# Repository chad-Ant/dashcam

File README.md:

# dashcam
Dashcam software for my own car. Hardware includes:
 - 1 IMX296 color camera facing front for recording and inference work, set at 1080p@60fps
 - 2 USB cameras for range finding, 360p@10fps
 - 1 USB camera for driver behavior, 360p@10fps

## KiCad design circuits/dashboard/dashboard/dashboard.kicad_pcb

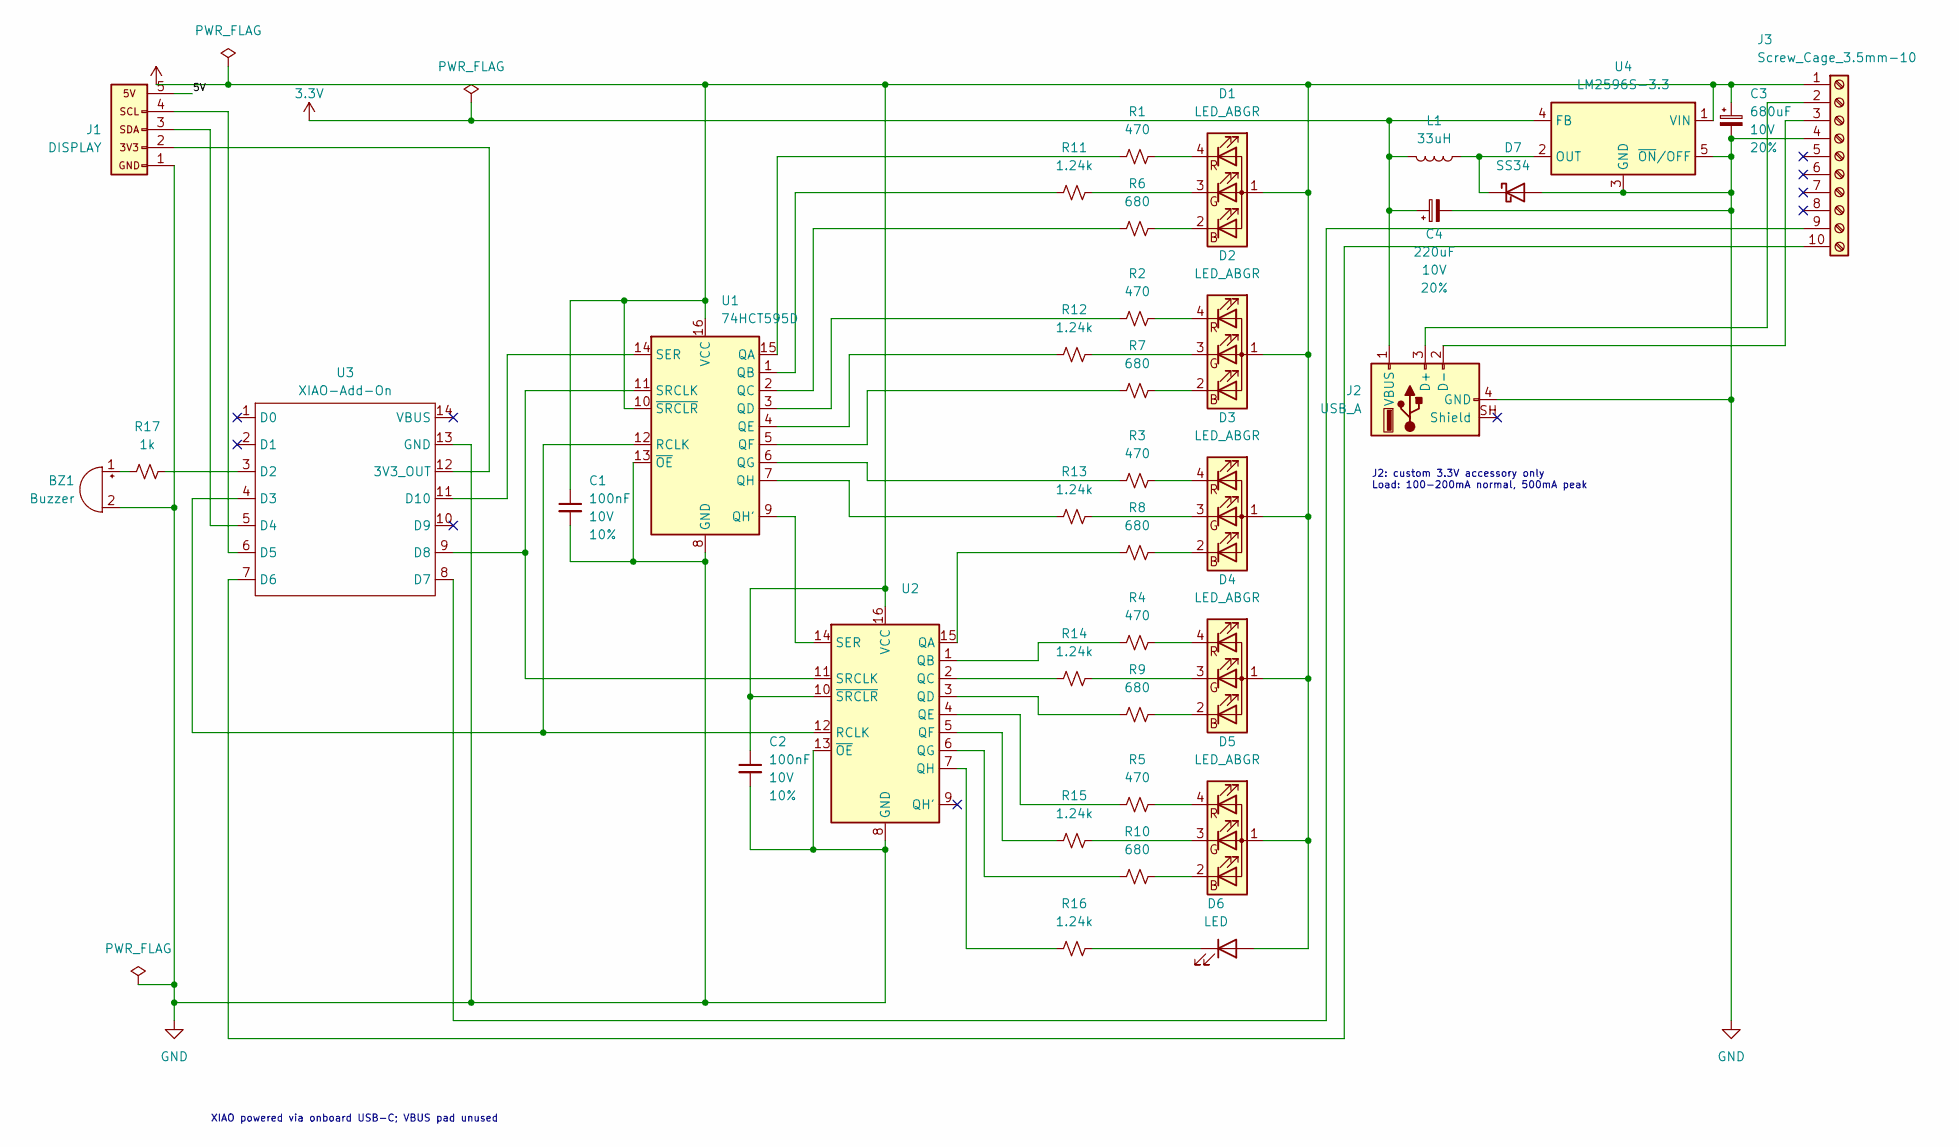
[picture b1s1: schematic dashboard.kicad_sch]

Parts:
BZ1: Buzzer; Buzzer_D14mm_H7mm_P10mm
C1, C2: 100nF; C_0805_2012Metric_Pad1.18x1.45mm_HandSolder; Voltage 10V; Tolerance 10%
C3: 680uF; CP_Elec_8x10.5; Voltage 10V; Tolerance 20%; MPN EEEFK1A681P
C4: 220uF; CP_Elec_8x6.2; Voltage 10V; Tolerance 20%; MPN EEEFK1A221P
D1, D2, D3, D4, D5: LED_ABGR; LED_RGB_5mm_ARGB_P2.54_HomeEtch
D6: LED; LED_D3mm_1mmDrill
D7: SS34; D_SMC
J1: DISPLAY; Display_Header_5pin
J2: USB_A; USB_A_SparkFun_Numbered
J3: Screw_Cage_3.5mm-10; TerminalBlock_Right_10pin_2p54
L1: 33uH; L_Bourns_SRR1260; MPN SRR1260-330M
R1, R2, R3, R4, R5: 470; R_0805_2012Metric_Pad1.20x1.40mm_HandSolder
R6, R7, R8, R9, R10: 680; R_0805_2012Metric_Pad1.20x1.40mm_HandSolder
R11, R12, R13, R14, R15, R16: 1.24k; R_0805_2012Metric_Pad1.20x1.40mm_HandSolder
R17: 1k; R_0805_2012Metric_Pad1.20x1.40mm_HandSolder
U1, U2: 74HCT595D; SOIC-16_3.9x9.9mm_P1.27mm
U3: XIAO-Add-On; XIAO_ESP32_C3
U4: LM2596S-3.3; TO-263-5_TabPin3

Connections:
3.3V: C4.1, J2.1 (VBUS), L1.2, U4.4 (FB)
5V: C1.1, C2.1, C3.1, D1.1 (A), D2.1 (A), D3.1 (A), D4.1 (A), D5.1 (A), D6.2 (A), J1.5, J3.1, U1.10 (~SRCLR), U1.16 (VCC), U2.10 (~SRCLR), U2.16 (VCC), U4.1 (VIN)
GND: BZ1.2 (-), C1.2, C2.2, C3.2, C4.2, D7.2 (A), J1.1, J2.4 (GND), J3.4, U1.8 (GND), U1.13 (~OE), U2.8 (GND), U2.13 (~OE), U3.13 (GND), U4.3 (GND), U4.5 (~ON/OFF)
unnamed: BZ1.1 (+), R17.1
unnamed: D1.2 (BK), R6.2
unnamed: D1.3 (GK), R11.2
unnamed: D1.4 (RK), R1.2
unnamed: D2.2 (BK), R7.2
unnamed: D2.3 (GK), R12.2
unnamed: D2.4 (RK), R2.2
unnamed: D3.2 (BK), R8.2
unnamed: D3.3 (GK), R13.2
unnamed: D3.4 (RK), R3.2
unnamed: D4.2 (BK), R9.2
unnamed: D4.3 (GK), R14.2
unnamed: D4.4 (RK), R4.2
unnamed: D5.2 (BK), R10.2
unnamed: D5.3 (GK), R15.2
unnamed: D5.4 (RK), R5.2
unnamed: D6.1 (K), R16.2
unnamed: D7.1 (K), L1.1, U4.2 (OUT)
unnamed: J1.2, U3.12 (3V3_OUT)
unnamed: J1.3, U3.5 (D4)
unnamed: J1.4, U3.6 (D5)
unnamed: J2.3 (D+), J3.2
unnamed 25: J2.2 (D-), J3.3; also elsewhere on the board
unnamed: R1.1, U1.15 (QA)
unnamed: R11.1, U1.1 (QB)
unnamed: R6.1, U1.2 (QC)
unnamed: R2.1, U1.3 (QD)
unnamed: R12.1, U1.4 (QE)
unnamed: R7.1, U1.5 (QF)
unnamed: R3.1, U1.6 (QG)
unnamed 33: U1.9 (QH'), U2.14 (SER); also elsewhere on the board
unnamed: R13.1, U1.7 (QH)
unnamed 35: U1.12 (RCLK), U2.12 (RCLK), U3.4 (D3); also elsewhere on the board
unnamed: U1.14 (SER), U3.11 (D10)
unnamed: U1.11 (SRCLK), U2.11 (SRCLK), U3.9 (D8)
unnamed 38: R8.1, U2.15 (QA); also elsewhere on the board
unnamed: R4.1, U2.1 (QB)
unnamed: R14.1, U2.2 (QC)
unnamed: R9.1, U2.3 (QD)
unnamed 42: R5.1, U2.4 (QE); also elsewhere on the board
unnamed: R15.1, U2.5 (QF)
unnamed: R10.1, U2.6 (QG)
unnamed: R16.1, U2.7 (QH)
unnamed: R17.2, U3.3 (D2)
unnamed: J3.10 (Pin_1), U3.7 (D6)
unnamed: J3.9 (Pin_1), U3.8 (D7)

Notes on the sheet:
XIAO powered via onboard USB-C; VBUS pad unused
J2: custom 3.3V accessory only Load: 100-200mA normal, 500mA peak

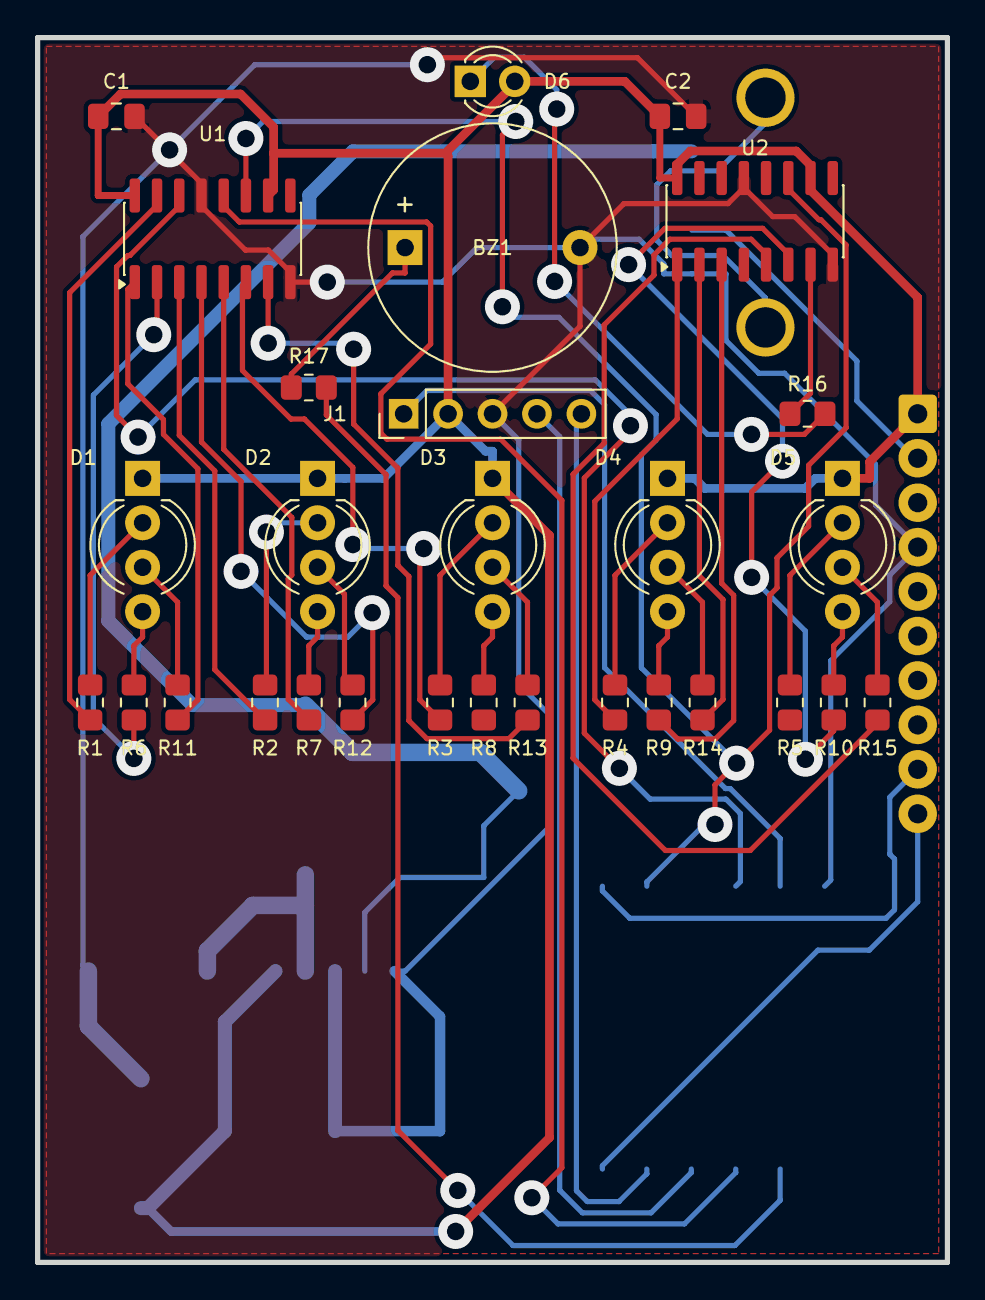
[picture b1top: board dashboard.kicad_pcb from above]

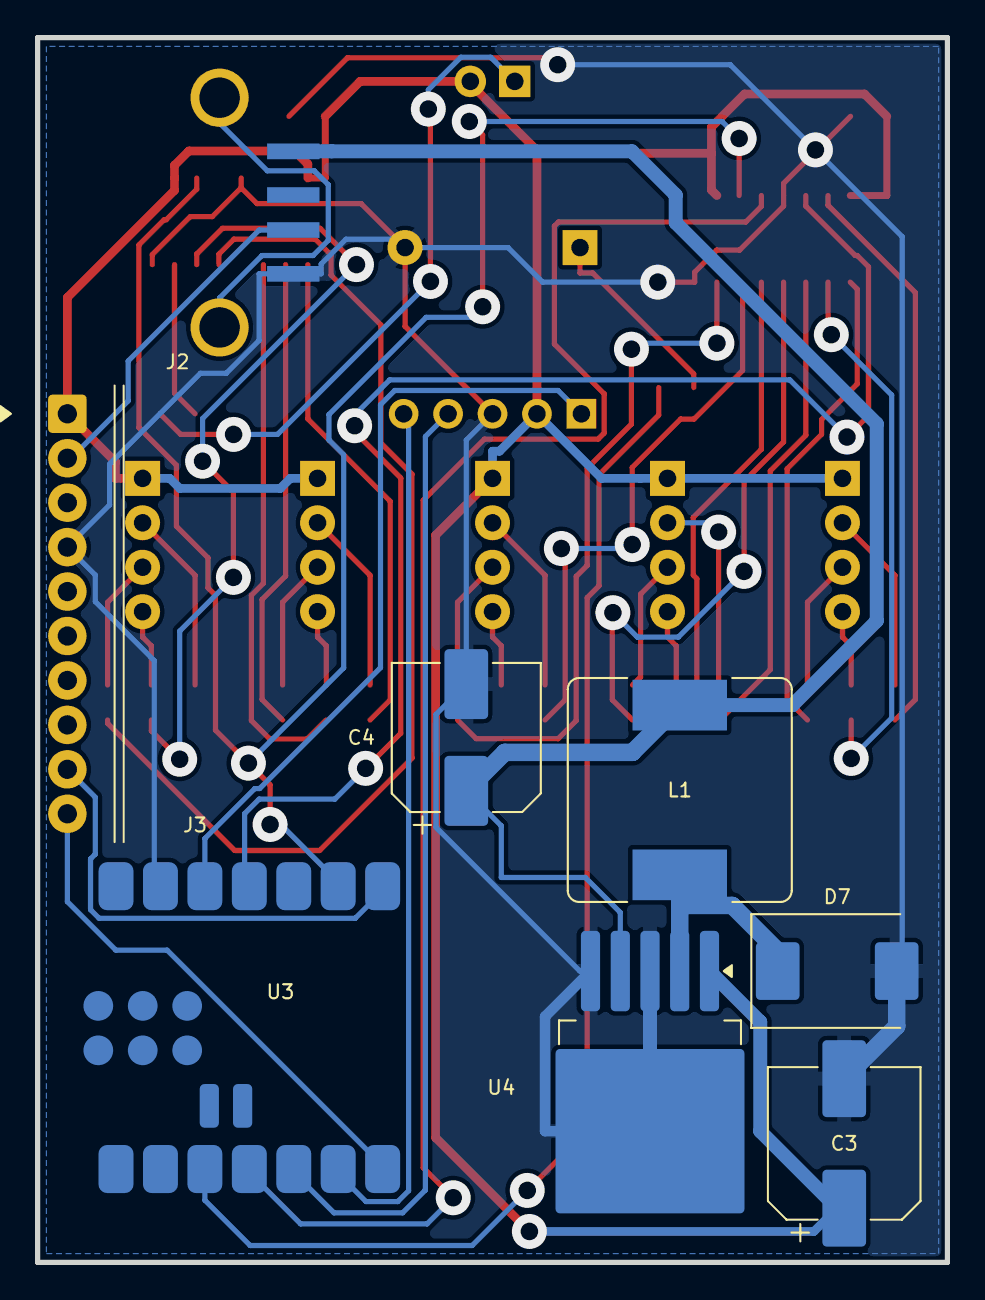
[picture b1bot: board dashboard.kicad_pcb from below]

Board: 2 copper layers, 52.0 x 70.0 mm, 42 parts (8 on the bottom side), 49 nets.

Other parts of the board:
WL1: INSULATED WIRE - FIT; Wire_Link_1
WL2: INSULATED WIRE - FIT; Wire_Link_2
WL3: INSULATED WIRE - FIT; Wire_Link_3
WL4: INSULATED WIRE - FIT; Wire_Link_4
WL5: INSULATED WIRE - FIT; Wire_Link_5

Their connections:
unnamed 25: WL5.1; also elsewhere on the board
unnamed 33: WL3.1; also elsewhere on the board
unnamed 35: WL2.1; also elsewhere on the board
unnamed 38: WL4.1; also elsewhere on the board
unnamed 42: WL1.1; also elsewhere on the board

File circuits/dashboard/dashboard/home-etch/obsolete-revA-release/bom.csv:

Reference,Quantity,Value,Manufacturer,MPN,Footprint,Side,Datasheet,Notes
BZ1,1,Buzzer,,,Buzzer_Beeper:Buzzer_D14mm_H7mm_P10mm,Front,,Exact ordering code not supplied; verify mechanical drawing against footprint before fabrication.
C1,1,100nF,,,dashboard:C_0603_1608Metric,Back,https://cdn.sparkfun.com/assets/8/a/4/a/5/Kemet_Capacitor_Da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,
C2,1,100nF,,,dashboard:C_0603_1608Metric,Back,https://cdn.sparkfun.com/assets/8/a/4/a/5/Kemet_Capacitor_Da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,
C3,1,680uF,Panasonic,EEUFR1A681,Capacitor_THT:CP_Radial_D8.0mm_P3.50mm,Back,https://industrial.panasonic.com/ww/products/pt/aluminum-cap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,
C4,1,220uF,Panasonic,EEUFR1A221,Capacitor_THT:CP_Radial_D6.3mm_P2.50mm,Back,https://industrial.panasonic.com/ww/products/pt/aluminum-cap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,
D1,1,LED_ABGR,,,"TerminalBlock_Phoenix:TerminalBlock_Phoenix_PT-1,5-4-3.5-H_1x04_P3.50mm_Horizontal",Front,,3.5 mm pitch; match Phoenix PT-1.5 horizontal footprint.
D2,1,LED_ABGR,,,"TerminalBlock_Phoenix:TerminalBlock_Phoenix_PT-1,5-4-3.5-H_1x04_P3.50mm_Horizontal",Front,,3.5 mm pitch; match Phoenix PT-1.5 horizontal footprint.
D3,1,LED_ABGR,,,"TerminalBlock_Phoenix:TerminalBlock_Phoenix_PT-1,5-4-3.5-H_1x04_P3.50mm_Horizontal",Front,,3.5 mm pitch; match Phoenix PT-1.5 horizontal footprint.
D4,1,LED_ABGR,,,"TerminalBlock_Phoenix:TerminalBlock_Phoenix_PT-1,5-4-3.5-H_1x04_P3.50mm_Horizontal",Front,,3.5 mm pitch; match Phoenix PT-1.5 horizontal footprint.
D5,1,LED_ABGR,,,"TerminalBlock_Phoenix:TerminalBlock_Phoenix_PT-1,5-4-3.5-H_1x04_P3.50mm_Horizontal",Front,,3.5 mm pitch; match Phoenix PT-1.5 horizontal footprint.
D6,1,LED,,,"TerminalBlock_Phoenix:TerminalBlock_Phoenix_PT-1,5-2-3.5-H_1x02_P3.50mm_Horizontal",Front,,3.5 mm pitch; match Phoenix PT-1.5 horizontal footprint.
D7,1,SS34,Vishay,SS34-M3/57T,Diode_SMD:D_SMC,Back,https://www.vishay.com/docs/88751/ss32.pdf,
J1,1,I2C,,,dashboard:I2C_Header_1x04,Front,,
J2,1,USB_A,,,dashboard:USB_A_SparkFun_Numbered,Front,,"Exact ordering code not supplied; verify mechanical drawing against footprint before fabrication. Custom 3.3 V output, not standard 5 V USB."
J3,1,Screw_Cage_3.5mm-10,,,dashboard:TerminalBlock_1x10_3p5,Front,https://cdn.sparkfun.com/assets/b/9/7/3/6/19854.pdf,Exact ordering code not supplied; verify mechanical drawing against footprint before fabrication.
L1,1,33uH,Bourns,SRR1260-330M,Inductor_SMD:L_Bourns_SRR1260,Back,https://www.bourns.com/docs/product-datasheets/srr1260.pdf,
R1,1,470,,,dashboard:R_0402_1005Metric,Front,https://www.vishay.com/docs/20035/dcrcwe3.pdf,
R2,1,470,,,dashboard:R_0402_1005Metric,Front,https://www.vishay.com/docs/20035/dcrcwe3.pdf,
R3,1,470,,,dashboard:R_0402_1005Metric,Front,https://www.vishay.com/docs/20035/dcrcwe3.pdf,
R4,1,470,,,dashboard:R_0402_1005Metric,Front,https://www.vishay.com/docs/20035/dcrcwe3.pdf,
R5,1,470,,,dashboard:R_0402_1005Metric,Front,https://www.vishay.com/docs/20035/dcrcwe3.pdf,
R6,1,680,,,dashboard:R_0402_1005Metric,Front,https://www.vishay.com/docs/20035/dcrcwe3.pdf,
R7,1,680,,,dashboard:R_0402_1005Metric,Front,https://www.vishay.com/docs/20035/dcrcwe3.pdf,
R8,1,680,,,dashboard:R_0402_1005Metric,Front,https://www.vishay.com/docs/20035/dcrcwe3.pdf,
R9,1,680,,,dashboard:R_0402_1005Metric,Front,https://www.vishay.com/docs/20035/dcrcwe3.pdf,
R10,1,680,,,dashboard:R_0402_1005Metric,Front,https://www.vishay.com/docs/20035/dcrcwe3.pdf,
R11,1,1.24k,,,dashboard:R_0603_1608Metric,Front,https://www.vishay.com/docs/20035/dcrcwe3.pdf,
R12,1,1.24k,,,dashboard:R_0603_1608Metric,Front,https://www.vishay.com/docs/20035/dcrcwe3.pdf,
R13,1,1.24k,,,dashboard:R_0603_1608Metric,Front,https://www.vishay.com/docs/20035/dcrcwe3.pdf,
R14,1,1.24k,,,dashboard:R_0603_1608Metric,Front,https://www.vishay.com/docs/20035/dcrcwe3.pdf,
R15,1,1.24k,,,dashboard:R_0603_1608Metric,Front,https://www.vishay.com/docs/20035/dcrcwe3.pdf,
R16,1,1.24k,,,dashboard:R_0603_1608Metric,Front,https://www.vishay.com/docs/20035/dcrcwe3.pdf,
R17,1,1k,,,dashboard:R_0402_1005Metric,Back,https://www.vishay.com/docs/20035/dcrcwe3.pdf,
U1,1,74HCT595DB,Nexperia,74HCT595DB,Package_SO:SSOP-16_5.3x6.2mm_P0.65mm,Back,https://www.nexperia.com/product/74HCT595DB,
U2,1,74HCT595DB,Nexperia,74HCT595DB,Package_SO:SSOP-16_5.3x6.2mm_P0.65mm,Back,https://www.nexperia.com/product/74HCT595DB,
U3,1,XIAO-Add-On,,,dashboard:XIAO_ESP32_C3,Front,,
U4,1,LM2596S-3.3,Texas Instruments,LM2596S-3.3,Package_TO_SOT_SMD:TO-263-5_TabPin3,Back,http://www.ti.com/lit/ds/symlink/lm2596.pdf,

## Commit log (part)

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2026-03-29 libcamera initial implement
2026-03-29 bugfixes
2026-05-01 libcamera and AI assist update
2026-05-01 add main, bug fixes
2026-05-01 Update README with hardware details
    Added hardware specifications for the dashcam setup.
2026-05-01 minor fixes and skill tweak
2026-05-02 thread safety changes
2026-05-03 prepare for libcamera test
2026-05-03 major fixes
2026-05-03 performance improvement
2026-05-03 minor bugfix for libcamera_csi
2026-05-10 refactoring and add other libs
2026-05-11 add gpio and CAN interface
2026-05-12 cleanup + libmidi
